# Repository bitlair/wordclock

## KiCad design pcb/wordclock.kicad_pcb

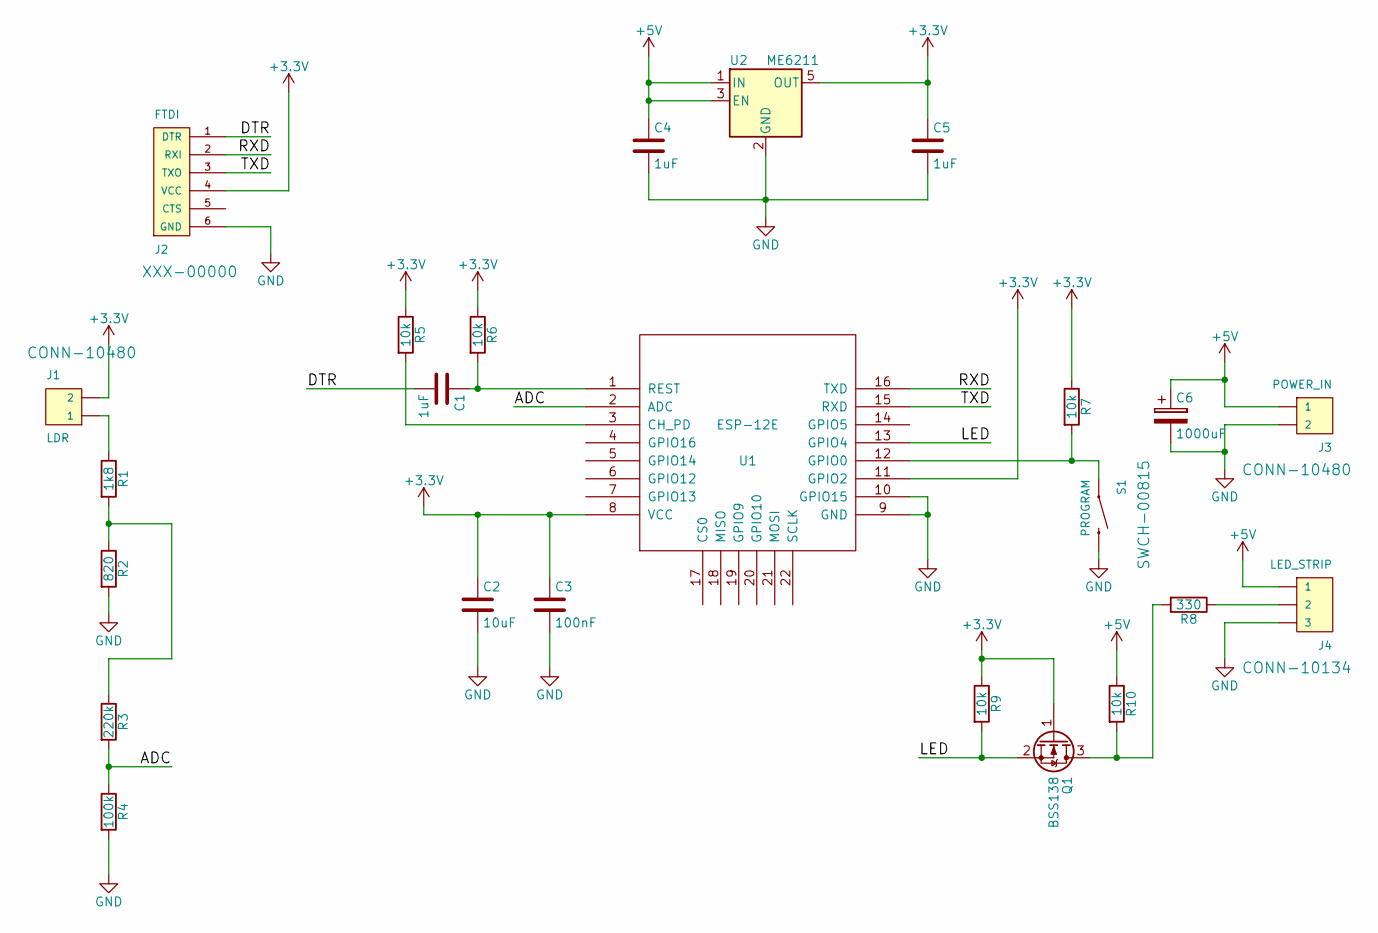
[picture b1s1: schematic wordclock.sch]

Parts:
C1, C4, C5: 1uF; C_0805
C2: 10uF; C_0805
C3: 100nF; C_0805
C6: 1000uF; CP_Radial_Tantal_D8.0mm_P2.50mm
J1: LDR; 1X02_SMD_SOLDER_PADS
J2: FTDI; MOLEX-1X6_LOCK
J3: POWER_IN; 1X02_SMD_SOLDER_PADS
J4: LED_STRIP; 1X03_SMD_SOLDER_PADS
Q1: BSS138; SOT-23
R1: 1k8; R_0805
R2: 820; R_0805
R3: 220k; R_0805
R4: 100k; R_0805
R5, R6, R7, R9, R10: 10k; R_0805
R8: 330; R_0805
S1: PROGRAM; TACTILE_SWITCH_SMD_6.0X3.5MM
U1: ESP-12E; ESP-12E_SMD
U2: ME6211; SOT-23-5

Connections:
+3V3: C2.1, C3.1, C5.1, J1.2, J2.4 (VCC), Q1.1 (G), R5.1, R6.1, R7.1, R9.1, U1.8 (VCC), U1.11 (GPIO2), U2.5 (OUT)
+5V: C4.1, C6.1, J3.1, J4.1, R10.1, U2.1 (IN), U2.3 (EN)
/ADC: R3.2, R4.1, U1.2 (ADC)
/DTR: C1.2, J2.1 (DTR)
/LED: Q1.2 (S), R9.2, U1.13 (GPIO4)
/RXD: J2.2 (RXI), U1.16 (TXD)
/TXD: J2.3 (TXO), U1.15 (RXD)
GND: C2.2, C3.2, C4.2, C5.2, C6.2, J2.6 (GND), J3.2, J4.3, R2.2, R4.2, S1.2, U1.9 (GND), U1.10 (GPIO15), U2.2 (GND)
unnamed: C1.1, R6.2, U1.1 (REST)
unnamed: J1.1, R1.1
unnamed: J4.2, R8.1
unnamed: Q1.3 (D), R8.2, R10.2
unnamed: R1.2, R2.1, R3.1
unnamed: R5.2, U1.3 (CH_PD)
unnamed: R7.2, S1.1, U1.12 (GPIO0)

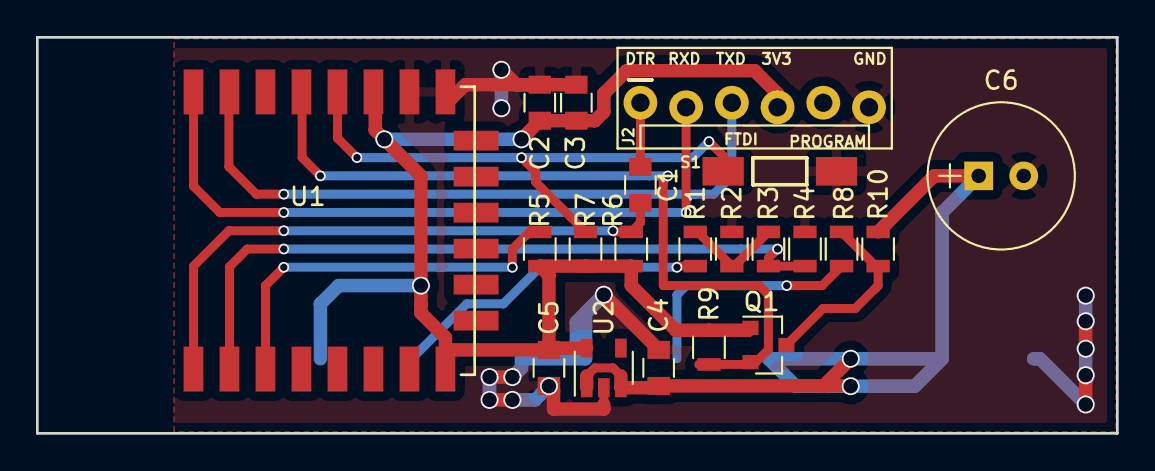
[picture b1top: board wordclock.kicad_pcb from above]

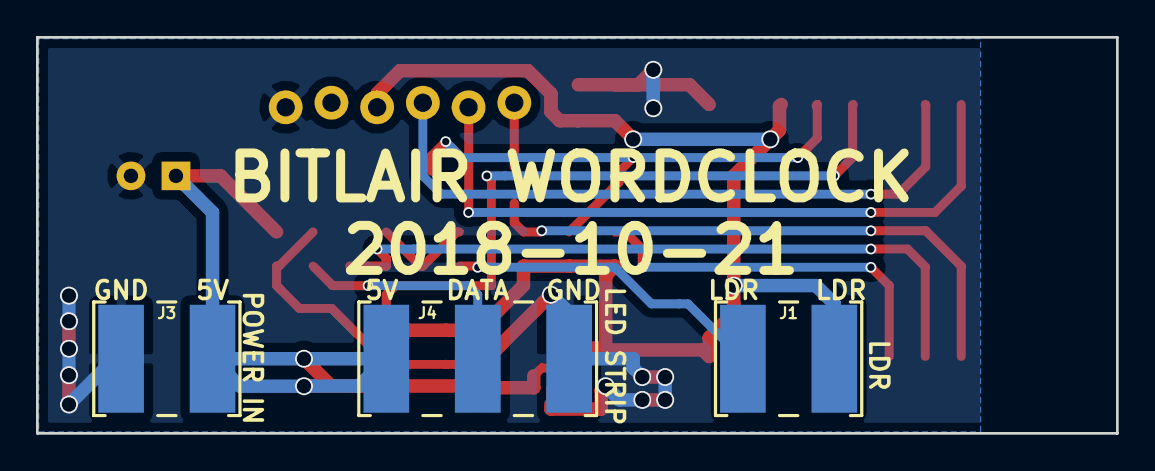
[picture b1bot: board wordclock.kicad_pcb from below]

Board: 2 copper layers, 60.0 x 22.0 mm, 24 parts (3 on the bottom side), 15 nets.

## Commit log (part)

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2018-10-14 Start with Arduino sketch.
2018-11-18 Start access point when wifi not configured or available.
2018-11-21 Adjusted captive portal detection.
2018-12-02 NTP time retrieval.
2018-12-23 Added leds.
2019-01-13 Initial install of vue for UI
2019-01-15 Added some page styling.
2019-01-18 Added background to hue slider.
2019-01-19 Added firmware update option and led brightness setting.
2019-01-19 Added advanced settings for firmware update and brightness setting.
2019-01-19 Different way of excluding checksum from checksum calculation.
2019-01-20 Added mDNS and option to change in UI.
2019-01-20 Added test interface.
2019-01-20 Disabled mDNS.
2019-01-20 Updated interface.
2019-01-20 Removed unused map files.
2019-01-20 Fix language errors
2019-01-20 Fix language error
2019-01-20 More language fixes.
2019-01-20 Updated interface with language fixes.
2019-01-23 presentatie en fotos
2019-01-23 Add clockfaces/lasercut-frame/pcb
2019-01-25 Clockface fix.
2019-01-26 added eventinfra and hackintheclass to presentation
2019-10-06 Bump axios from 0.18.0 to 0.18.1 in /html
    Bumps [axios](https://github.com/axios/axios) from 0.18.0 to 0.18.1.
    - [Release notes](https://github.com/axios/axios/releases)
    - [Changelog](https://github.com/axios/axios/blob/v0.18.1/CHANGELOG.md)
    - [Commits](https://github.com/axios/axios/compare/v0.18.0...v0.18.1)
2019-10-06 Bump webpack-bundle-analyzer from 3.0.3 to 3.5.2 in /html
    Bumps [webpack-bundle-analyzer](https://github.com/webpack-contrib/webpack-bundle-analyzer) from 3.0.3 to 3.5.2.
    - [Release notes](https://github.com/webpack-contrib/webpack-bundle-analyzer/releases)
    - [Changelog](https://github.com/webpack-contrib/webpack-bundle-analyzer/blob/master/CHANGELOG.md)
    - [Commits](https://github.com/webpack-contrib/webpack-bundle-analyzer/compare/v3.0.3...v3.5.2)
2019-10-06 Bump js-yaml from 3.12.1 to 3.13.1 in /html
    Bumps [js-yaml](https://github.com/nodeca/js-yaml) from 3.12.1 to 3.13.1.
    - [Release notes](https://github.com/nodeca/js-yaml/releases)
    - [Changelog](https://github.com/nodeca/js-yaml/blob/master/CHANGELOG.md)
    - [Commits](https://github.com/nodeca/js-yaml/compare/3.12.1...3.13.1)
2019-10-06 Bump lodash.defaultsdeep from 4.6.0 to 4.6.1 in /html
    Bumps [lodash.defaultsdeep](https://github.com/lodash/lodash) from 4.6.0 to 4.6.1.
    - [Release notes](https://github.com/lodash/lodash/releases)
    - [Commits](https://github.com/lodash/lodash/compare/4.6.0...4.6.1)
2019-10-06 Bump mixin-deep from 1.3.1 to 1.3.2 in /html
    Bumps [mixin-deep](https://github.com/jonschlinkert/mixin-deep) from 1.3.1 to 1.3.2.
    - [Release notes](https://github.com/jonschlinkert/mixin-deep/releases)
    - [Commits](https://github.com/jonschlinkert/mixin-deep/compare/1.3.1...1.3.2)
2019-10-06 Bump bootstrap from 4.2.1 to 4.3.1 in /html
    Bumps [bootstrap](https://github.com/twbs/bootstrap) from 4.2.1 to 4.3.1.
    - [Release notes](https://github.com/twbs/bootstrap/releases)
    - [Commits](https://github.com/twbs/bootstrap/compare/v4.2.1...v4.3.1)
2019-10-06 Bump lodash from 4.17.11 to 4.17.15 in /html
    Bumps [lodash](https://github.com/lodash/lodash) from 4.17.11 to 4.17.15.
    - [Release notes](https://github.com/lodash/lodash/releases)
    - [Commits](https://github.com/lodash/lodash/compare/4.17.11...4.17.15)
2020-06-06 Bump websocket-extensions from 0.1.3 to 0.1.4 in /html
    Bumps [websocket-extensions](https://github.com/faye/websocket-extensions-node) from 0.1.3 to 0.1.4.
    - [Release notes](https://github.com/faye/websocket-extensions-node/releases)
    - [Changelog](https://github.com/faye/websocket-extensions-node/blob/master/CHANGELOG.md)
    - [Commits](https://github.com/faye/websocket-extensions-node/compare/0.1.3...0.1.4)
2020-07-16 Bump lodash from 4.17.11 to 4.17.19 in /html
    Bumps [lodash](https://github.com/lodash/lodash) from 4.17.11 to 4.17.19.
    - [Release notes](https://github.com/lodash/lodash/releases)
    - [Commits](https://github.com/lodash/lodash/compare/4.17.11...4.17.19)
2020-07-30 Bump elliptic from 6.4.1 to 6.5.3 in /html
    Bumps [elliptic](https://github.com/indutny/elliptic) from 6.4.1 to 6.5.3.
    - [Release notes](https://github.com/indutny/elliptic/releases)
    - [Commits](https://github.com/indutny/elliptic/compare/v6.4.1...v6.5.3)
2021-01-05 Bump axios from 0.18.0 to 0.21.1 in /html
    Bumps [axios](https://github.com/axios/axios) from 0.18.0 to 0.21.1.
    - [Release notes](https://github.com/axios/axios/releases)
    - [Changelog](https://github.com/axios/axios/blob/v0.21.1/CHANGELOG.md)
    - [Commits](https://github.com/axios/axios/compare/v0.18.0...v0.21.1)
2021-01-06 Bump dot-prop from 4.2.0 to 4.2.1 in /html
    Bumps [dot-prop](https://github.com/sindresorhus/dot-prop) from 4.2.0 to 4.2.1.
    - [Release notes](https://github.com/sindresorhus/dot-prop/releases)
    - [Commits](https://github.com/sindresorhus/dot-prop/compare/v4.2.0...v4.2.1)
2021-01-06 Bump bootstrap-vue from 2.0.0-rc.11 to 2.0.0-rc.12 in /html
    Bumps [bootstrap-vue](https://github.com/bootstrap-vue/bootstrap-vue) from 2.0.0-rc.11 to 2.0.0-rc.12.
    - [Release notes](https://github.com/bootstrap-vue/bootstrap-vue/releases)
    - [Changelog](https://github.com/bootstrap-vue/bootstrap-vue/blob/dev/CHANGELOG-OLD.md)
    - [Commits](https://github.com/bootstrap-vue/bootstrap-vue/compare/v2.0.0-rc.11...v2.0.0-rc.12)
2021-01-06 Bump bootstrap from 4.2.1 to 4.5.3 in /html
    Bumps [bootstrap](https://github.com/twbs/bootstrap) from 4.2.1 to 4.5.3.
    - [Release notes](https://github.com/twbs/bootstrap/releases)
    - [Commits](https://github.com/twbs/bootstrap/compare/v4.2.1...v4.5.3)
2021-03-09 Bump elliptic from 6.4.1 to 6.5.4 in /html
    Bumps [elliptic](https://github.com/indutny/elliptic) from 6.4.1 to 6.5.4.
    - [Release notes](https://github.com/indutny/elliptic/releases)
    - [Commits](https://github.com/indutny/elliptic/compare/v6.4.1...v6.5.4)
2021-03-30 Bump y18n from 4.0.0 to 4.0.1 in /html
    Bumps [y18n](https://github.com/yargs/y18n) from 4.0.0 to 4.0.1.
    - [Release notes](https://github.com/yargs/y18n/releases)
    - [Changelog](https://github.com/yargs/y18n/blob/master/CHANGELOG.md)
    - [Commits](https://github.com/yargs/y18n/commits)
2021-05-08 Bump lodash from 4.17.11 to 4.17.21 in /html
    Bumps [lodash](https://github.com/lodash/lodash) from 4.17.11 to 4.17.21.
    - [Release notes](https://github.com/lodash/lodash/releases)
    - [Commits](https://github.com/lodash/lodash/compare/4.17.11...4.17.21)
2021-05-09 Bump hosted-git-info from 2.7.1 to 2.8.9 in /html
    Bumps [hosted-git-info](https://github.com/npm/hosted-git-info) from 2.7.1 to 2.8.9.
    - [Release notes](https://github.com/npm/hosted-git-info/releases)
    - [Changelog](https://github.com/npm/hosted-git-info/blob/v2.8.9/CHANGELOG.md)
    - [Commits](https://github.com/npm/hosted-git-info/compare/v2.7.1...v2.8.9)
2021-05-27 Bump dns-packet from 1.3.1 to 1.3.4 in /html
    Bumps [dns-packet](https://github.com/mafintosh/dns-packet) from 1.3.1 to 1.3.4.
    - [Release notes](https://github.com/mafintosh/dns-packet/releases)
    - [Changelog](https://github.com/mafintosh/dns-packet/blob/master/CHANGELOG.md)
    - [Commits](https://github.com/mafintosh/dns-packet/compare/v1.3.1...v1.3.4)
2021-06-04 Bump ws from 6.1.2 to 6.2.2 in /html
    Bumps [ws](https://github.com/websockets/ws) from 6.1.2 to 6.2.2.
    - [Release notes](https://github.com/websockets/ws/releases)
    - [Commits](https://github.com/websockets/ws/commits)
    ---
    updated-dependencies:
    - dependency-name: ws
2021-08-10 Bump path-parse from 1.0.6 to 1.0.7 in /html
    Bumps [path-parse](https://github.com/jbgutierrez/path-parse) from 1.0.6 to 1.0.7.
    - [Release notes](https://github.com/jbgutierrez/path-parse/releases)
    - [Commits](https://github.com/jbgutierrez/path-parse/commits/v1.0.7)
    ---
    updated-dependencies:
    - dependency-name: path-parse
2022-01-13 Bump follow-redirects from 1.6.1 to 1.14.7 in /html
    Bumps [follow-redirects](https://github.com/follow-redirects/follow-redirects) from 1.6.1 to 1.14.7.
    - [Release notes](https://github.com/follow-redirects/follow-redirects/releases)
    - [Commits](https://github.com/follow-redirects/follow-redirects/compare/v1.6.1...v1.14.7)
    ---
    updated-dependencies:
    - dependency-name: follow-redirects
2022-02-12 Bump follow-redirects from 1.6.1 to 1.14.8 in /html
    Bumps [follow-redirects](https://github.com/follow-redirects/follow-redirects) from 1.6.1 to 1.14.8.
    - [Release notes](https://github.com/follow-redirects/follow-redirects/releases)
    - [Commits](https://github.com/follow-redirects/follow-redirects/compare/v1.6.1...v1.14.8)
    ---
    updated-dependencies:
    - dependency-name: follow-redirects
2022-02-17 Bump url-parse from 1.4.4 to 1.5.7 in /html
    Bumps [url-parse](https://github.com/unshiftio/url-parse) from 1.4.4 to 1.5.7.
    - [Release notes](https://github.com/unshiftio/url-parse/releases)
    - [Commits](https://github.com/unshiftio/url-parse/compare/1.4.4...1.5.7)
    ---
    updated-dependencies:
    - dependency-name: url-parse
2022-02-26 Bump url-parse from 1.4.4 to 1.5.10 in /html
    Bumps [url-parse](https://github.com/unshiftio/url-parse) from 1.4.4 to 1.5.10.
    - [Release notes](https://github.com/unshiftio/url-parse/releases)
    - [Commits](https://github.com/unshiftio/url-parse/compare/1.4.4...1.5.10)
    ---
    updated-dependencies:
    - dependency-name: url-parse
2022-06-01 Bump eventsource from 1.0.7 to 1.1.1 in /html
    Bumps [eventsource](https://github.com/EventSource/eventsource) from 1.0.7 to 1.1.1.
    - [Release notes](https://github.com/EventSource/eventsource/releases)
    - [Changelog](https://github.com/EventSource/eventsource/blob/master/HISTORY.md)
    - [Commits](https://github.com/EventSource/eventsource/compare/v1.0.7...v1.1.1)
    ---
    updated-dependencies:
2022-06-22 Bump shell-quote from 1.6.1 to 1.7.3 in /html
    Bumps [shell-quote](https://github.com/substack/node-shell-quote) from 1.6.1 to 1.7.3.
    - [Release notes](https://github.com/substack/node-shell-quote/releases)
    - [Changelog](https://github.com/substack/node-shell-quote/blob/master/CHANGELOG.md)
    - [Commits](https://github.com/substack/node-shell-quote/compare/1.6.1...1.7.3)
    ---
    updated-dependencies:
2022-11-18 Bump loader-utils and @vue/cli-service in /html
    Bumps [loader-utils](https://github.com/webpack/loader-utils) to 1.4.2 and updates ancestor dependency [@vue/cli-service](https://github.com/vuejs/vue-cli/tree/HEAD/packages/@vue/cli-service). These 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
    Updates `loader-utils` from 1.2.3 to 1.4.2
    - [Release notes](https://github.com/webpack/loader-utils/releases)
    - [Changelog](https://github.com/webpack/loader-utils/blob/v1.4.2/CHANGELOG.md)
    - [Commits](https://github.com/webpack/loader-utils/compare/v1.2.3...v1.4.2)
    Updates `@vue/cli-service` from 3.2.3 to 5.0.8
2022-12-02 Bump decode-uri-component from 0.2.0 to 0.2.2 in /html
    Bumps [decode-uri-component](https://github.com/SamVerschueren/decode-uri-component) from 0.2.0 to 0.2.2.
    - [Release notes](https://github.com/SamVerschueren/decode-uri-component/releases)
    - [Commits](https://github.com/SamVerschueren/decode-uri-component/compare/v0.2.0...v0.2.2)
    ---
    updated-dependencies:
    - dependency-name: decode-uri-component
2022-12-09 Bump express from 4.16.4 to 4.18.2 in /html
    Bumps [express](https://github.com/expressjs/express) from 4.16.4 to 4.18.2.
    - [Release notes](https://github.com/expressjs/express/releases)
    - [Changelog](https://github.com/expressjs/express/blob/master/History.md)
    - [Commits](https://github.com/expressjs/express/compare/4.16.4...4.18.2)
    ---
    updated-dependencies:
